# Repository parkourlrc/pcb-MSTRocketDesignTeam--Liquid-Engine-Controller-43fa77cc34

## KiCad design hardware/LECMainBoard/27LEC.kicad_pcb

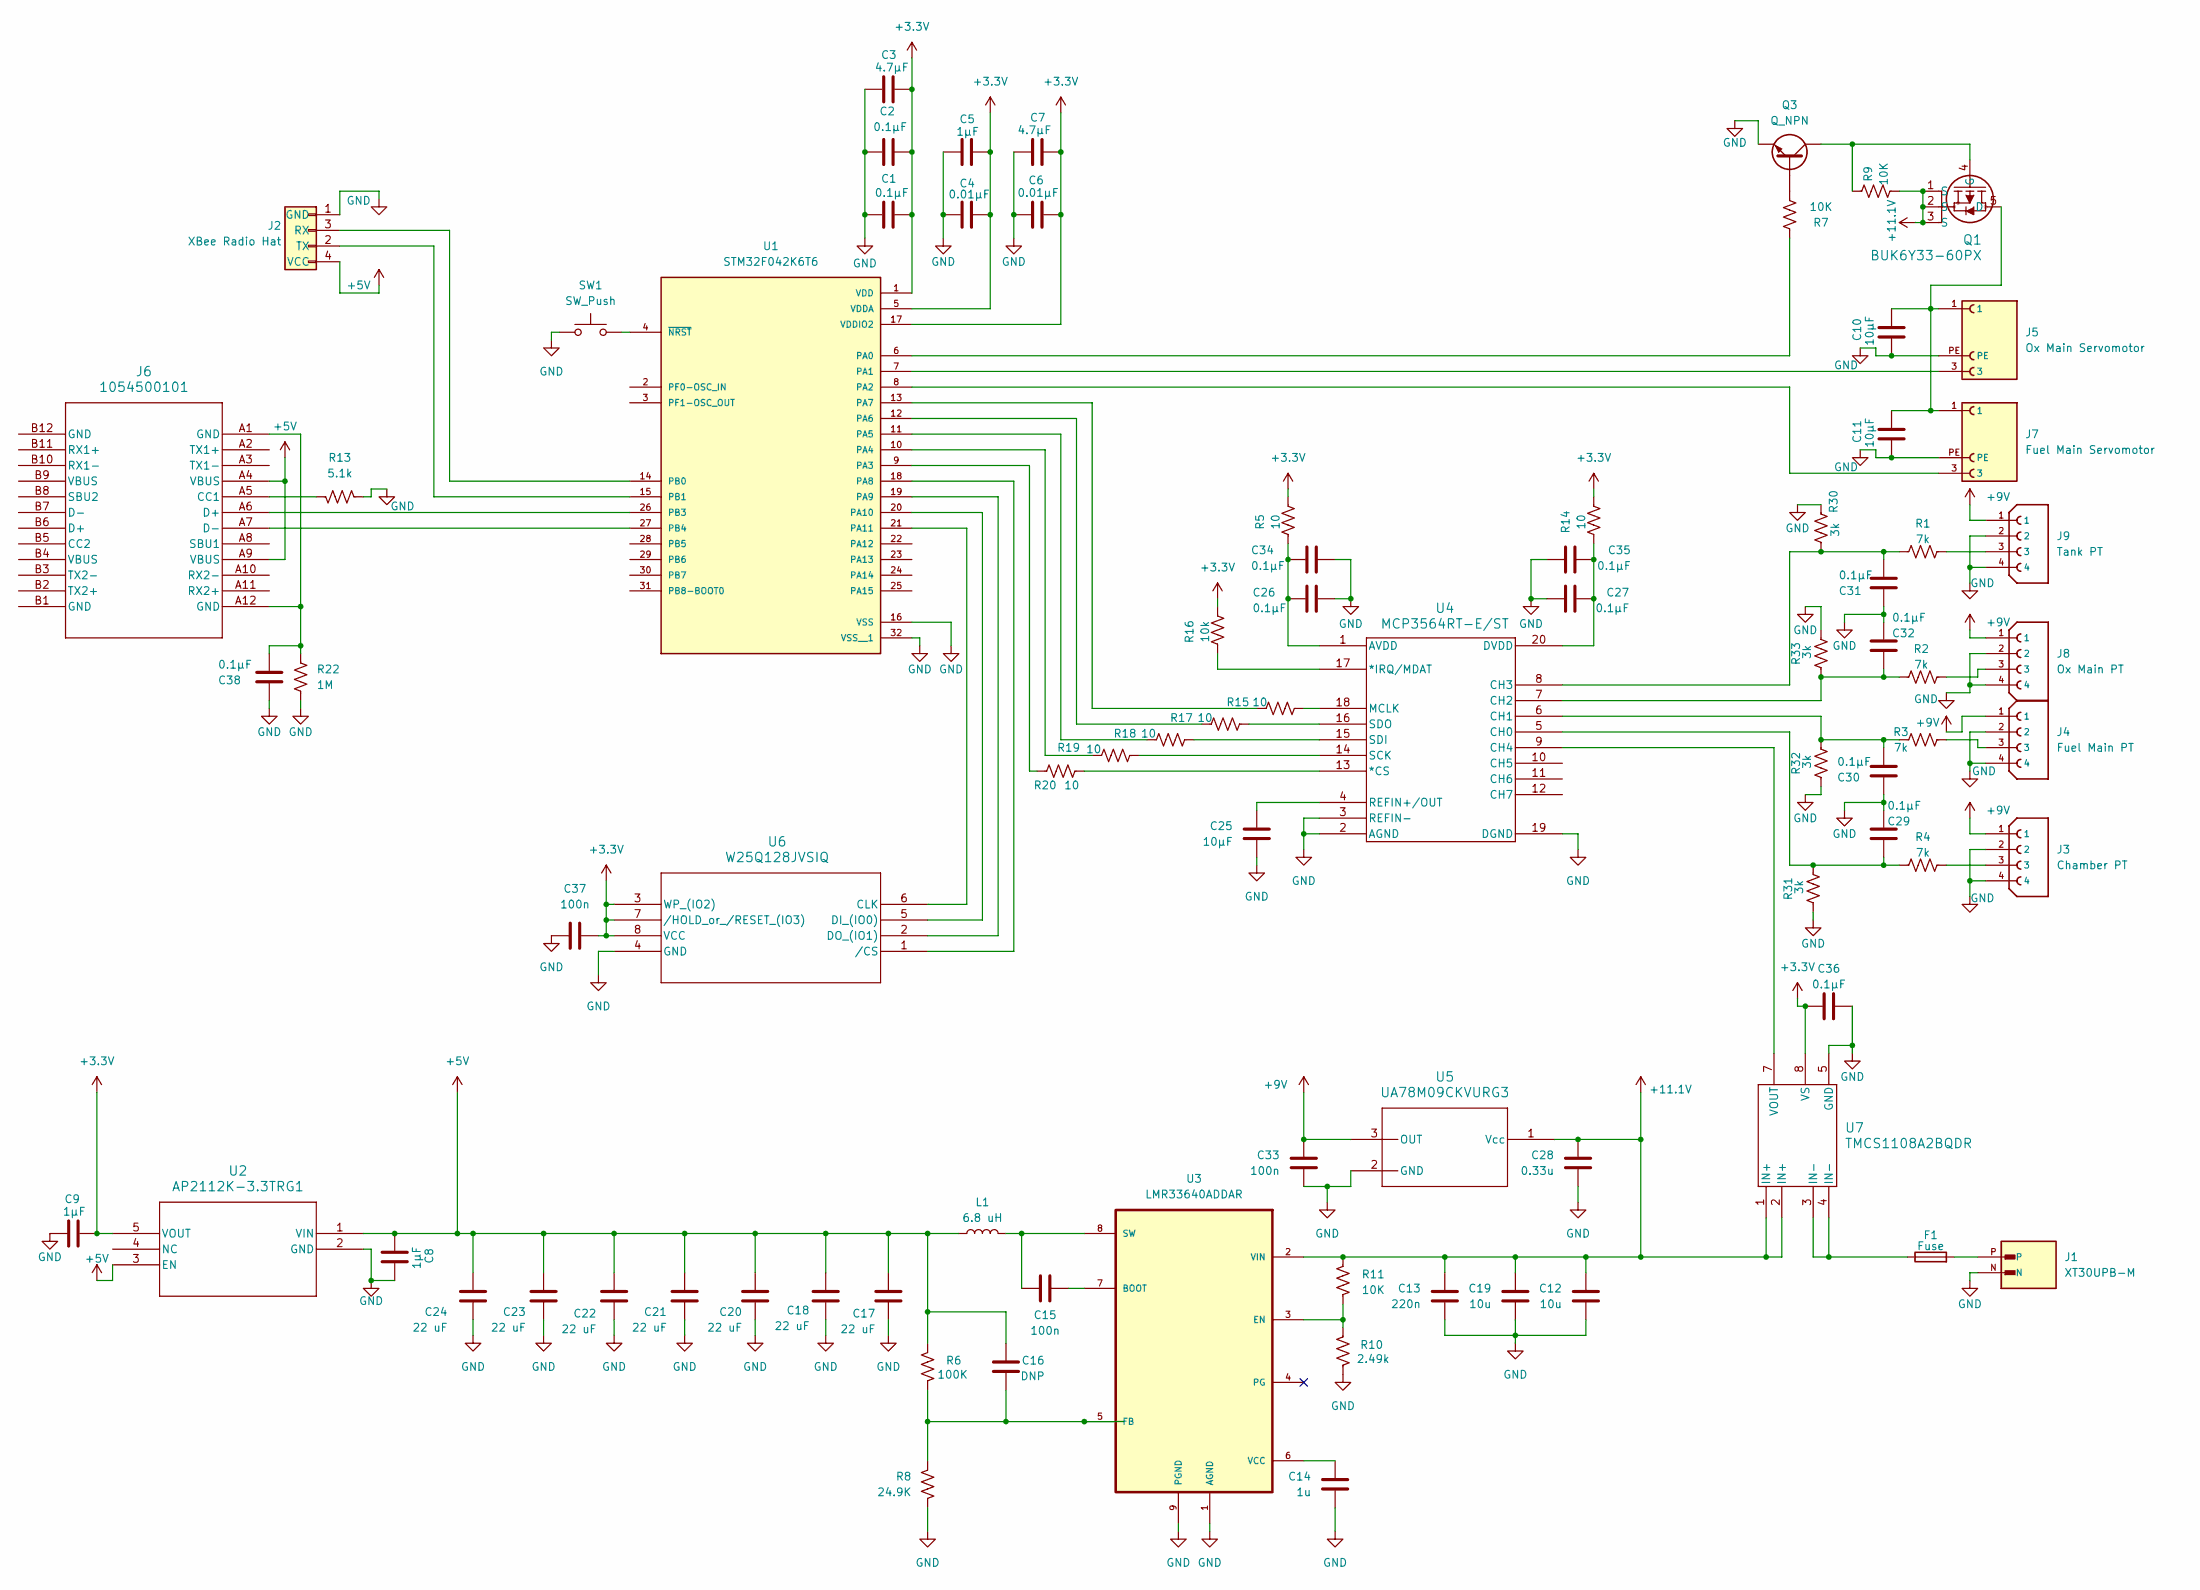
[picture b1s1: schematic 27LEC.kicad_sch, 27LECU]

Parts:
C1, C2: 0.1μF; C_0603_1608Metric
C3, C7: 4.7μF; C_0603_1608Metric
C4, C6: 0.01μF; C_0603_1608Metric
C5, C8, C9: 1μF; C_0603_1608Metric
C10, C11: 10μF; C_0603_1608Metric
C12, C19: 10u; C_1210_3225Metric
C13: 220n; C_0805_2012Metric
C14: 1u; C_0805_2012Metric
C15, C33, C37: 100n; C_0603_1608Metric
C16: DNP; C_0805_2012Metric
C17, C18, C20, C21, C22, C23, C24: 22 uF; C_0805_2012Metric
C25: 10μF; C_1210_3225Metric
C26, C27, C29, C30, C31, C32, C34, C35, C38: 0.1μF; C_1210_3225Metric
C28: 0.33u; C_1206_3216Metric
C36: 0.1μF; C_1206_3216Metric
F1: Fuse; FUS_SCHURTER_3413_SCH
J1: XT30UPB-M; AMASS_XT30UPB-M; MPN XT30UPB-M
J2: XBee Radio Hat; PinSocket_1x04_P2.54mm_Vertical
J3: Chamber PT; TENSILITY_54-00278; MPN 54-00278
J4: Fuel Main PT; TENSILITY_54-00278; MPN 54-00278
J5: Ox Main Servomotor; TENSILITY_54-00440; MPN 54-00440
J6: 1054500101; CONN_1054500101_MOL
J7: Fuel Main Servomotor; TENSILITY_54-00440; MPN 54-00440
J8: Ox Main PT; TENSILITY_54-00278; MPN 54-00278
J9: Tank PT; TENSILITY_54-00278; MPN 54-00278
L1: 6.8 uH; L_0603_1608Metric
Q1: BUK6Y33-60PX; LFPAK_SOT669_NEX
Q3: Q_NPN; SOT-323_SC-70
R1, R2, R3, R4: 7k; R_0603_1608Metric
R5, R14, R15, R17, R18, R19, R20: 10; R_0603_1608Metric
R6: 100K; R_0603_1608Metric
R7, R9, R11: 10K; R_0603_1608Metric
R8: 24.9K; R_0603_1608Metric
R10: 2.49k; R_0603_1608Metric
R13: 5.1k; R_0603_1608Metric
R16: 10k; R_0603_1608Metric
R22: 1M; R_0603_1608Metric
R30, R31, R32, R33: 3k; R_0603_1608Metric
SW1: SW_Push
U1: STM32F042K6T6; QFP80P900X900X160-32N; PARTREV 5
U2: AP2112K-3.3TRG1; SOT_RG1_DIO
U3: LMR33640ADDAR; Texas_HSOP-8-1EP_3.9x4.9mm_P1.27mm_ThermalVias
U4: MCP3564RT-E/ST; TSSOP20_ST_MCH
U5: UA78M09CKVURG3; TO-252-2
U6: W25Q128JVSIQ; SOIC_128JVSIQ_WIN
U7: TMCS1108A2BQDR; D0008A-IPC_B

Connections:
+3.3V: C1.1, C2.1, C3.1, C4.1, C5.1, C6.1, C7.1, C9.1, C36.2, C37.2, R5.2, R14.2, R16.2, U1.1 (VDD), U1.5 (VDDA), U1.17 (VDDIO2), U2.5 (VOUT), U6.3 (WP_(IO2)), U6.7 (/HOLD_or_/RESET_(IO3)), U6.8 (VCC), U7.8 (VS)
+5V: C8.2, C16.2, C17.1, C18.1, C20.1, C21.1, C22.1, C23.1, C24.1, J2.4 (VCC), J6.A4 (VBUS), J6.A9 (VBUS), L1.2, R6.2, U2.1 (VIN), U2.3 (EN)
+9V: C33.2, J3.1, J4.1, J8.1, J9.1, U5.3 (OUT)
+11.1V: C12.1, C13.1, C19.1, C28.2, Q1.1 (S), Q1.2 (S), Q1.3 (S), R9.1, R11.1, U3.2 (VIN), U5.1 (Vcc), U7.1 (IN+), U7.2 (IN+)
GND: C1.2, C2.2, C3.2, C4.2, C5.2, C6.2, C7.2, C8.1, C9.2, C10.2, C11.2, C12.2, C13.2, C14.2, C17.2, C18.2, C19.2, C20.2, C21.2, C22.2, C23.2, C24.2, C25.2, C26.1, C27.1, C28.1, C29.2, C30.1, C31.1, C32.2, C33.1, C34.1, C35.1, C36.1, C37.1, C38.2, J1.N, J2.1 (GND), J3.2, J3.4, J4.2, J4.4, J5.PE, J7.PE, J8.2, J8.4, J9.2, J9.4, Q3.2 (E), R8.2, R10.1, R13.1, R22.1, R30.2, R31.2, R32.2, R33.1, SW1.1, U1.16 (VSS), U1.32 (VSS__1), U2.2 (GND), U3.1 (AGND), U3.9 (PGND), U4.2 (AGND), U4.3 (REFIN-), U4.19 (DGND), U5.2 (GND), U6.4 (GND), U7.5 (GND)
unnamed: C38.1, J6.A1 (GND), J6.A12 (GND), R22.2
unnamed: F1.1, U7.3 (IN-), U7.4 (IN-)
unnamed: F1.2, J1.P
unnamed: J2.3 (RX), U1.14 (PB0)
unnamed: J2.2 (TX), U1.15 (PB1)
unnamed: J3.3, R4.2
unnamed: J4.3, R3.2
unnamed: J6.A5 (CC1), R13.2
unnamed: J8.3, R2.2
unnamed: J9.3, R1.2
unnamed: C10.1, C11.1, J5.1, J7.1, Q1.5 (D)
unnamed: Q1.4 (G), Q3.3 (C), R9.2
unnamed: Q3.1 (B), R7.1
unnamed: R7.2, U1.6 (PA0)
unnamed: J5.3, U1.7 (PA1)
unnamed: J7.3, U1.8 (PA2)
unnamed: R20.1, U1.9 (PA3)
unnamed: R19.1, U1.10 (PA4)
unnamed: R18.1, U1.11 (PA5)
unnamed: R17.1, U1.12 (PA6)
unnamed: R15.1, U1.13 (PA7)
unnamed: U1.18 (PA8), U6.1 (/CS)
unnamed: U1.19 (PA9), U6.2 (DO_(IO1))
unnamed: U1.20 (PA10), U6.5 (DI_(IO0))
unnamed: U1.21 (PA11), U6.6 (CLK)
unnamed: J6.A6 (D+), U1.26 (PB3)
unnamed: J6.A7 (D-), U1.27 (PB4)
unnamed: SW1.2, U1.4 (~NRST)
unnamed: C15.1, U3.7 (BOOT)
unnamed: R10.2, R11.2, U3.3 (EN)
unnamed: C16.1, R6.1, R8.1, U3.5 (FB)
unnamed: C15.2, L1.1, U3.8 (SW)
unnamed: C14.1, U3.6 (VCC)
unnamed: R20.2, U4.13 (*CS)
unnamed: R16.1, U4.17 (*IRQ/MDAT)
unnamed: C26.2, C34.2, R5.1, U4.1 (AVDD)
unnamed: C29.1, R4.1, R31.1, U4.5 (CH0)
unnamed: C30.2, R3.1, R32.1, U4.6 (CH1)
unnamed: C32.1, R2.1, R33.2, U4.7 (CH2)
unnamed: C31.2, R1.1, R30.1, U4.8 (CH3)
unnamed: U4.9 (CH4), U7.7 (VOUT)
unnamed: C27.2, C35.2, R14.1, U4.20 (DVDD)
unnamed: R15.2, U4.18 (MCLK)
unnamed: C25.1, U4.4 (REFIN+/OUT)
unnamed: R19.2, U4.14 (SCK)
unnamed: R18.2, U4.15 (SDI)
unnamed: R17.2, U4.16 (SDO)

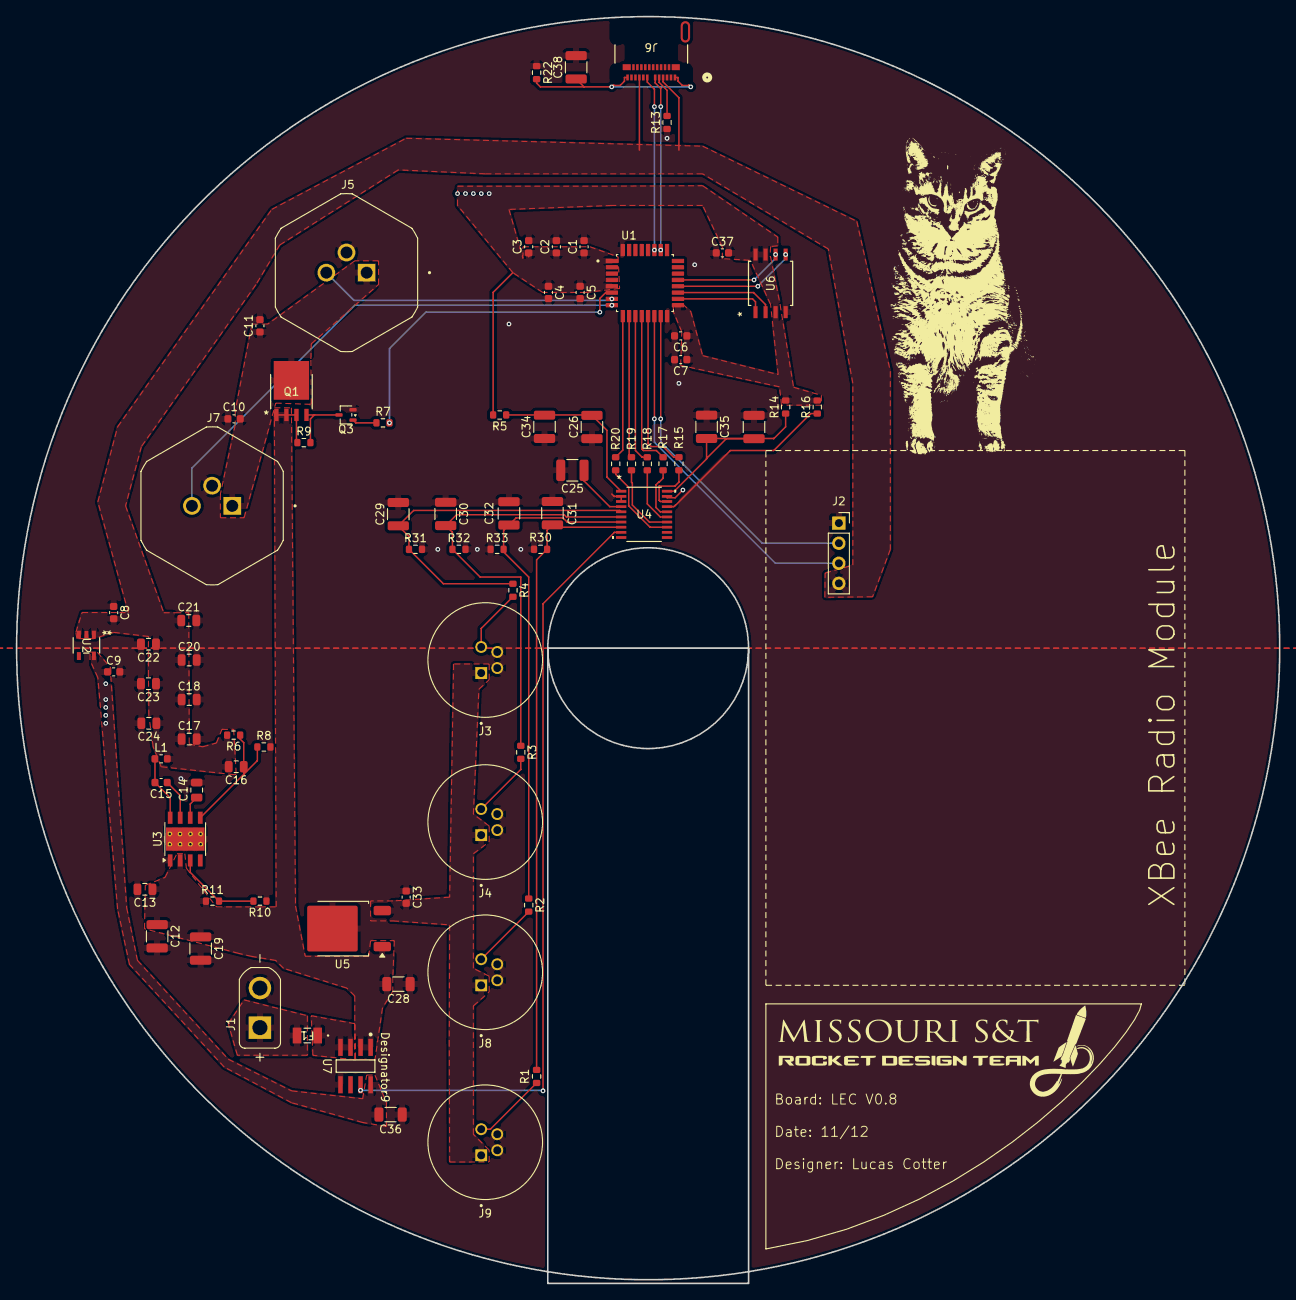
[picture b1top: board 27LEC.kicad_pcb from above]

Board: 2 copper layers, 159.8 x 159.8 mm, 82 parts (0 on the bottom side), 51 nets.
